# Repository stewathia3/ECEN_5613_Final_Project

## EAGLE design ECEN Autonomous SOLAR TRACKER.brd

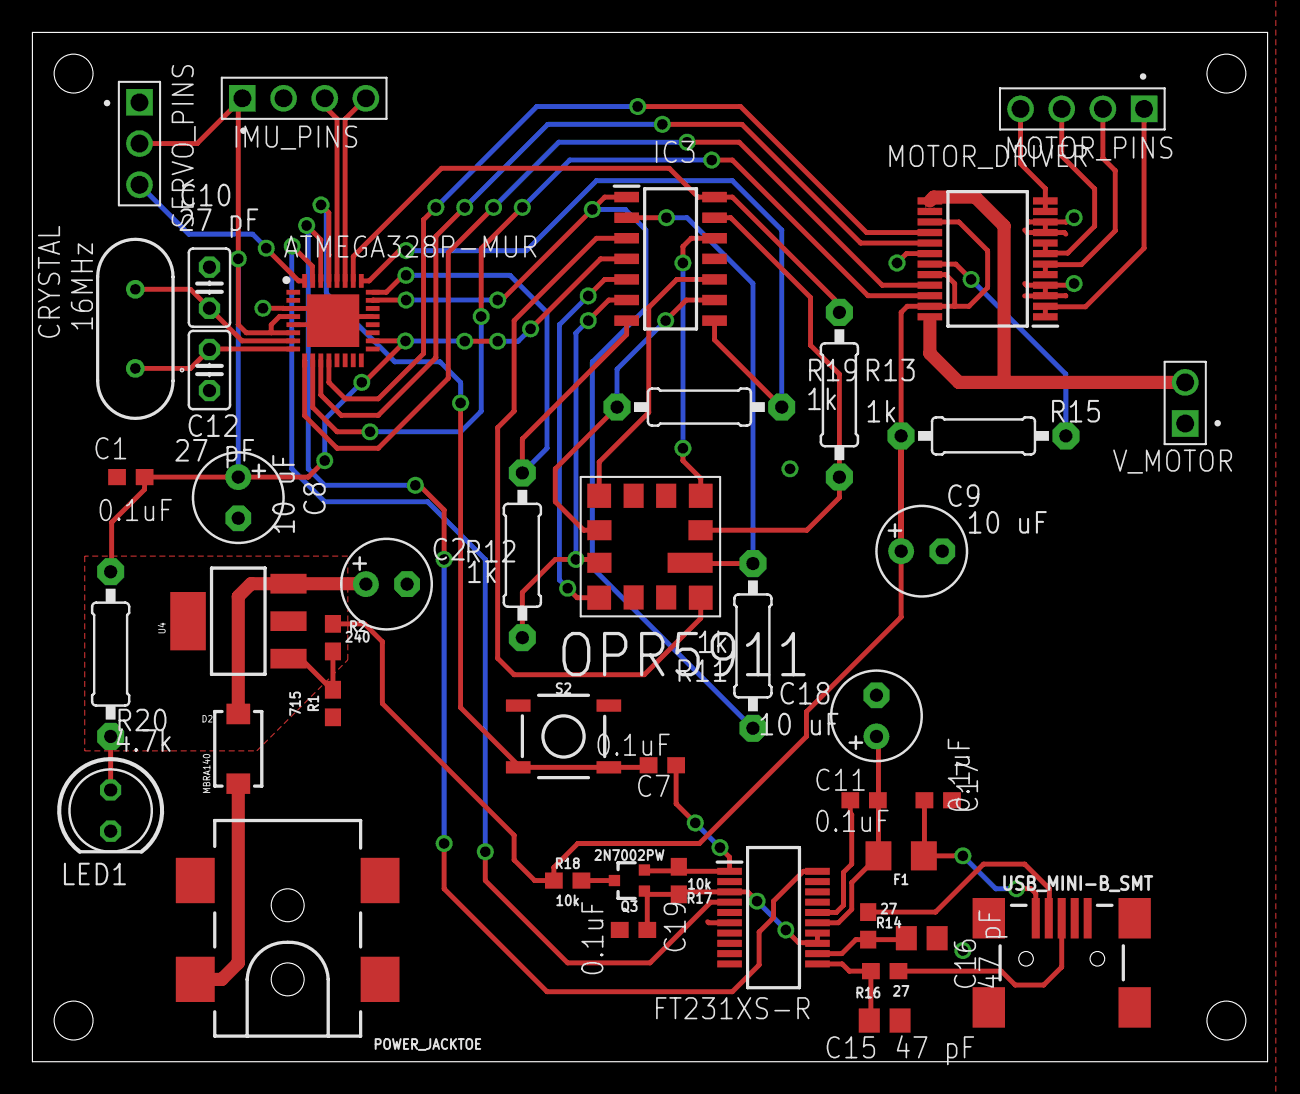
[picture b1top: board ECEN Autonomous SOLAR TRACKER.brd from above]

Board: 2 copper layers, 76.2 x 63.5 mm, 43 parts (0 on the bottom side), 45 nets.

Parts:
C1, C7, C11, C17, C19: 0.1uF; C0603
C2: 47 uF; E2,5-6
C8, C9, C18: 10 uF; E2,5-6
C10, C12: 27 pF; C025-025X050
C15, C16: 47 pF; C0805
CRYSTAL: 16MHz; HC49
D2: MBRA140; SMA-DIODE
F1: 6V/0.5A; 1206
IC1: ATMEGA328P-MUR; QFN50P500X500X100-33N
IC2: FT231XS-R; SOP64P599X175-20N
IC3: OPA4140AID; SOIC127P600X175-14N
J1: POWER_JACKTOE; POWER_JACK_SMD_OVERPASTE_TOE
J2: USB_MINI-B_SMT; USB-MINIB
J4: IMU_PINS; 61300411121
LED1: LED5MM
MOTOR_DRIVER: TB6612FNG,C,8,EL; SOP65P760X160-24N
MOTOR_PINS: 61300411121
OPR5911: OPR5911; OPR5911-12
Q3: 2N7002PW; SOT323
R1: 715; 0603
R2: 240; 0603
R11, R12, R13, R15, R19: 1k; 0207/10
R14, R16: 27; 0603
R17, R18: 10k; 0603
R20: 4.7k; 0207/10
S2: TACTILE_SWITCH_SMD_5.2MM
SERVO_PINS: 61300311121
U4: SOT223
V_MOTOR: 61300211121

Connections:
3V3OUT: C19.1, IC2.3, IC2.13, IC2.14, Q3.1, R17.2
+IN_A: IC3.3, OPR5911.2
+IN_B: IC3.5, OPR5911.5
+IN_C: IC3.10, OPR5911.8
+IN_D: IC3.12, OPR5911.11
A0: IC1.23, IC3.1, R11.1
A1: IC1.24, IC3.7, R12.1
A2: IC1.25, IC3.8, R19.2
A3: IC1.26, IC3.14, R13.2
A+: MOTOR_DRIVER.1, MOTOR_DRIVER.2, MOTOR_PINS.1
A-: MOTOR_DRIVER.5, MOTOR_DRIVER.6, MOTOR_PINS.2
AIN1: IC1.9, MOTOR_DRIVER.21
AIN2: IC1.10, MOTOR_DRIVER.22
B+: MOTOR_DRIVER.11, MOTOR_DRIVER.12, MOTOR_PINS.4
B-: MOTOR_DRIVER.7, MOTOR_DRIVER.8, MOTOR_PINS.3
BIN1: IC1.11, MOTOR_DRIVER.17
BIN2: IC1.12, MOTOR_DRIVER.16
DTR: C7.1, IC2.1, Q3.2, R17.1
GND: C1.2, C2.-, C8.-, C9.-, C10.2, C11.1, C12.1, C15.1, C16.1, C17.2, C18.-, C19.2, IC1.3, IC1.5, IC1.21, IC1.33, IC2.6, IC2.16, IC3.11, J1.GND, J2.GND, J2.S1, J2.S2, J2.S3, J2.S4, J4.2, LED1.K, MOTOR_DRIVER.3, MOTOR_DRIVER.4, MOTOR_DRIVER.9, MOTOR_DRIVER.10, MOTOR_DRIVER.18, R1.1, S2.1, S2.2, SERVO_PINS.1, V_MOTOR.1
unnamed: C2.+, D2.C, U4.3
unnamed: C15.2, IC2.11, R16.2
unnamed: D2.A, J1.VIN0
unnamed: LED1.A, R20.1
unnamed: IC3.2, OPR5911.1, R11.2
unnamed: R1.2, R2.1, U4.1
unnamed: C7.2, IC1.29, S2.3, S2.4
unnamed: C16.2, IC2.12, R14.2
unnamed: IC3.6, OPR5911.6, R12.2
unnamed: C10.1, CRYSTAL.2, IC1.7
unnamed: IC3.13, OPR5911.12, R13.1
unnamed: IC3.9, OPR5911.7, R19.1
unnamed: C12.2, CRYSTAL.1, IC1.8
unnamed: MOTOR_DRIVER.19, R15.2
unnamed: C17.1, F1.1, J2.VBUS
unnamed: J2.D-, R14.1
unnamed: J2.D+, R16.1
unnamed: C11.2, C18.+, F1.2, IC2.15
unnamed: Q3.3, R18.1
RX-I: IC1.30, IC2.20
SCL_3V: IC1.28, J4.3
SDA_3V: IC1.27, J4.4
SERVO_PWM: IC1.32, SERVO_PINS.3
TX-O: IC1.31, IC2.4
VIN: C1.1, C8.+, C9.+, IC1.4, IC1.6, IC1.18, IC3.4, J4.1, MOTOR_DRIVER.15, MOTOR_DRIVER.20, MOTOR_DRIVER.23, R2.2, R15.1, R18.2, R20.2, SERVO_PINS.2, U4.2, U4.4
VMOTOR: MOTOR_DRIVER.13, MOTOR_DRIVER.14, MOTOR_DRIVER.24, V_MOTOR.2

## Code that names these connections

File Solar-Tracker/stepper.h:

/*
 * Sanjana Tewathia
 * ECEN 5613 - Fall 2020 - Prof. McClure
 * University of Colorado Boulder
 * Revised 12/6/20
 *
 * C include file for the stepper motor driver
 */

#ifndef STEPPER_H_INCLUDED
#define STEPPER_H_INCLUDED
#define AIN1 5
#define AIN2 6
#define BIN1 7
#define BIN2 0

#define DELAY 1

/****************************************************************************************************************
@function: void stepper_init(): initializes stepper motor
@param :    void
@return:    void
*****************************************************************************************************/
void init_stepper();
/****************************************************************************************************************
@function: void stepper_loop): runs the code for stepper to move in desired directions
@param :    void
@return:    void
*****************************************************************************************************/
void stepper_loop();

#endif // STEPPER_H_INCLUDED

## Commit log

2020-12-04 Add files via upload
    Haven't tested this code yet, but it should work!
2020-12-05 comit two
2020-12-05 Create main.c
    servo code
2020-12-05 commit 2
2020-12-06 COMMIT TWO
2020-12-06 commit5
2020-12-07 commit 6
2020-12-07 commit next
2020-12-08 FINAL FINAL COMMIT
2020-12-09 Final

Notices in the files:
parts and their libraries:
SparkFun-Fuses: Licensing: Creative Commons ShareAlike 4.0 International - https://creativecommons.org/licenses/by-sa/4.0
